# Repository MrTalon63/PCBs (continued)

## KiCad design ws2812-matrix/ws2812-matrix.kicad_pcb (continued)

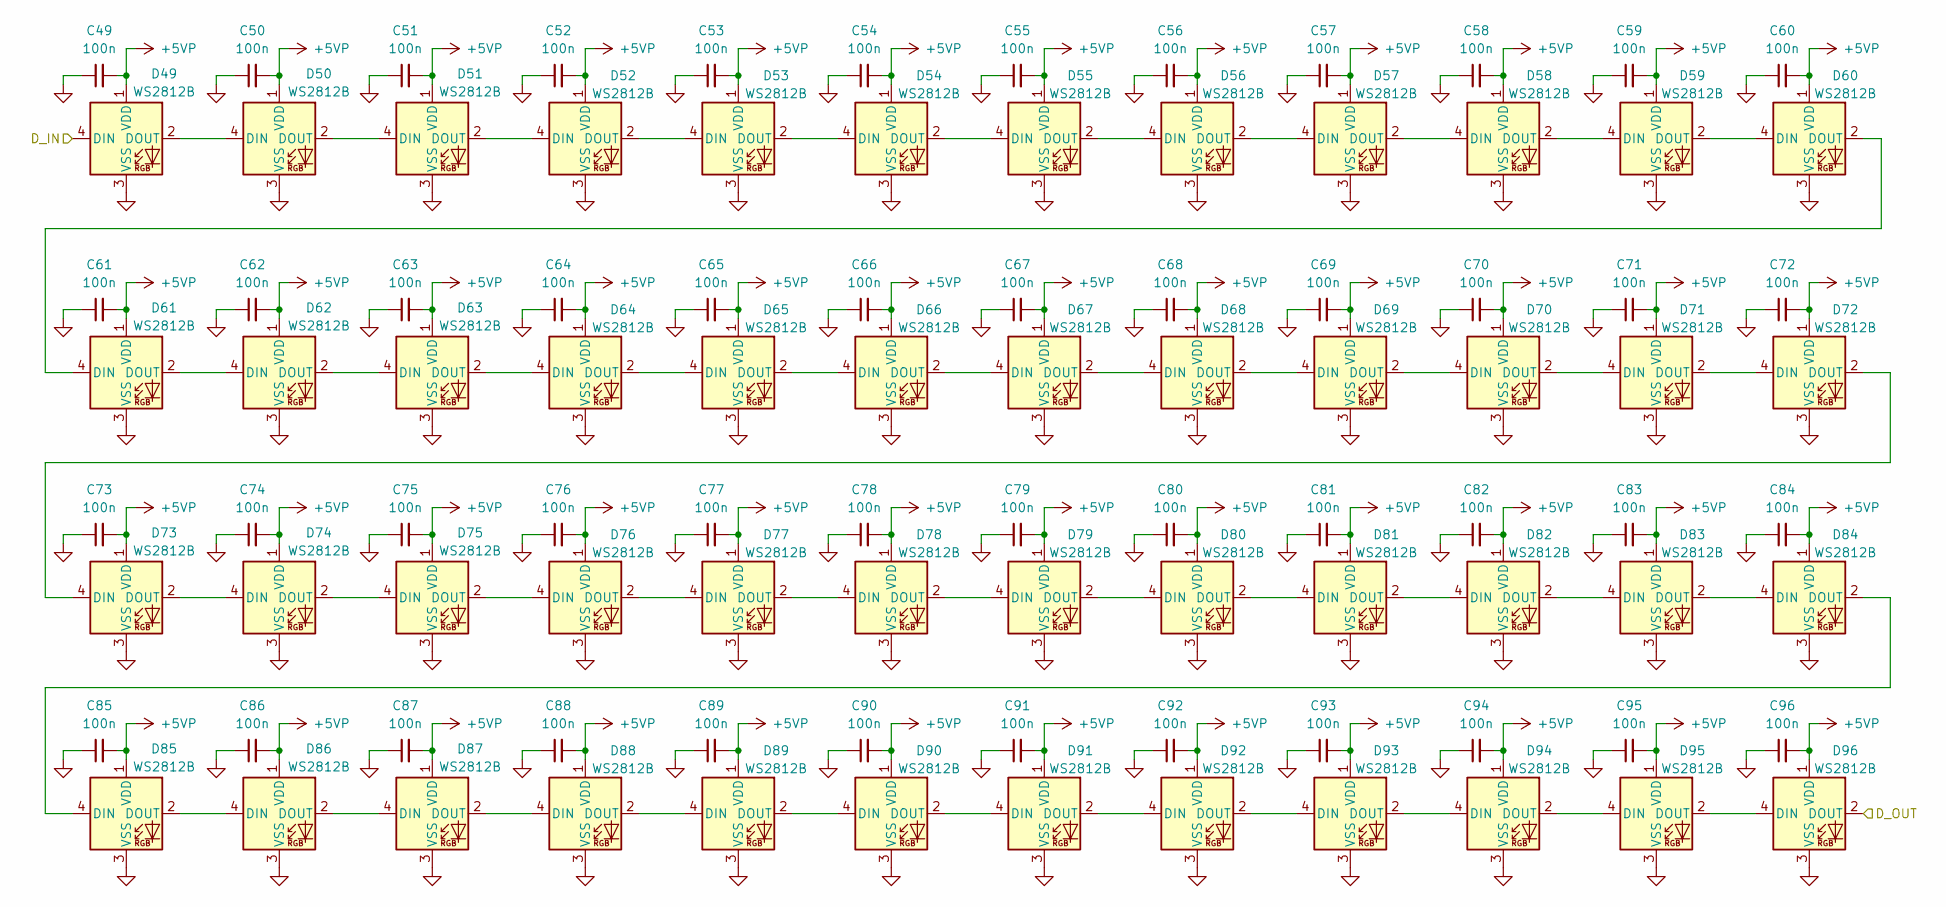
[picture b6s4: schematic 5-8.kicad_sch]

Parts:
C49, C50, C51, C52, C53, C54, C55, C56, C57, C58, C59, C60, C61, C62, C63, C64, C65, C66, C67, C68, C69, C70, C71, C72, C73, C74, C75, C76, C77, C78, C79, C80, C81, C82, C83, C84, C85, C86, C87, C88, C89, C90, C91, C92, C93, C94, C95, C96: 100n; C_0402_1005Metric
D49, D50, D51, D52, D53, D54, D55, D56, D57, D58, D59, D60, D61, D62, D63, D64, D65, D66, D67, D68, D69, D70, D71, D72, D73, D74, D75, D76, D77, D78, D79, D80, D81, D82, D83, D84, D85, D86, D87, D88, D89, D90, D91, D92, D93, D94, D95, D96: WS2812B; LED_WS2812B_PLCC4_5.0x5.0mm_P3.2mm

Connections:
+5VP: C49.2, C50.2, C51.2, C52.2, C53.2, C54.2, C55.2, C56.2, C57.2, C58.2, C59.2, C60.2, C61.2, C62.2, C63.2, C64.2, C65.2, C66.2, C67.2, C68.2, C69.2, C70.2, C71.2, C72.2, C73.2, C74.2, C75.2, C76.2, C77.2, C78.2, C79.2, C80.2, C81.2, C82.2, C83.2, C84.2, C85.2, C86.2, C87.2, C88.2, C89.2, C90.2, C91.2, C92.2, C93.2, C94.2, C95.2, C96.2, D49.1 (VDD), D50.1 (VDD), D51.1 (VDD), D52.1 (VDD), D53.1 (VDD), D54.1 (VDD), D55.1 (VDD), D56.1 (VDD), D57.1 (VDD), D58.1 (VDD), D59.1 (VDD), D60.1 (VDD), D61.1 (VDD), D62.1 (VDD), D63.1 (VDD), D64.1 (VDD), D65.1 (VDD), D66.1 (VDD), D67.1 (VDD), D68.1 (VDD), D69.1 (VDD), D70.1 (VDD), D71.1 (VDD), D72.1 (VDD), D73.1 (VDD), D74.1 (VDD), D75.1 (VDD), D76.1 (VDD), D77.1 (VDD), D78.1 (VDD), D79.1 (VDD), D80.1 (VDD), D81.1 (VDD), D82.1 (VDD), D83.1 (VDD), D84.1 (VDD), D85.1 (VDD), D86.1 (VDD), D87.1 (VDD), D88.1 (VDD), D89.1 (VDD), D90.1 (VDD), D91.1 (VDD), D92.1 (VDD), D93.1 (VDD), D94.1 (VDD), D95.1 (VDD), D96.1 (VDD); also elsewhere on the board
/LEDs/1-4/D_OUT: D49.4 (DIN); also elsewhere on the board
/LEDs/5-8/D_OUT: D96.2 (DOUT); also elsewhere on the board
GND: C49.1, C50.1, C51.1, C52.1, C53.1, C54.1, C55.1, C56.1, C57.1, C58.1, C59.1, C60.1, C61.1, C62.1, C63.1, C64.1, C65.1, C66.1, C67.1, C68.1, C69.1, C70.1, C71.1, C72.1, C73.1, C74.1, C75.1, C76.1, C77.1, C78.1, C79.1, C80.1, C81.1, C82.1, C83.1, C84.1, C85.1, C86.1, C87.1, C88.1, C89.1, C90.1, C91.1, C92.1, C93.1, C94.1, C95.1, C96.1, D49.3 (VSS), D50.3 (VSS), D51.3 (VSS), D52.3 (VSS), D53.3 (VSS), D54.3 (VSS), D55.3 (VSS), D56.3 (VSS), D57.3 (VSS), D58.3 (VSS), D59.3 (VSS), D60.3 (VSS), D61.3 (VSS), D62.3 (VSS), D63.3 (VSS), D64.3 (VSS), D65.3 (VSS), D66.3 (VSS), D67.3 (VSS), D68.3 (VSS), D69.3 (VSS), D70.3 (VSS), D71.3 (VSS), D72.3 (VSS), D73.3 (VSS), D74.3 (VSS), D75.3 (VSS), D76.3 (VSS), D77.3 (VSS), D78.3 (VSS), D79.3 (VSS), D80.3 (VSS), D81.3 (VSS), D82.3 (VSS), D83.3 (VSS), D84.3 (VSS), D85.3 (VSS), D86.3 (VSS), D87.3 (VSS), D88.3 (VSS), D89.3 (VSS), D90.3 (VSS), D91.3 (VSS), D92.3 (VSS), D93.3 (VSS), D94.3 (VSS), D95.3 (VSS), D96.3 (VSS); also elsewhere on the board
unnamed: D49.2 (DOUT), D50.4 (DIN)
unnamed: D50.2 (DOUT), D51.4 (DIN)
unnamed: D51.2 (DOUT), D52.4 (DIN)
unnamed: D52.2 (DOUT), D53.4 (DIN)
unnamed: D53.2 (DOUT), D54.4 (DIN)
unnamed: D54.2 (DOUT), D55.4 (DIN)
unnamed: D55.2 (DOUT), D56.4 (DIN)
unnamed: D56.2 (DOUT), D57.4 (DIN)
unnamed: D57.2 (DOUT), D58.4 (DIN)
unnamed: D58.2 (DOUT), D59.4 (DIN)
unnamed: D59.2 (DOUT), D60.4 (DIN)
unnamed: D60.2 (DOUT), D61.4 (DIN)
unnamed: D61.2 (DOUT), D62.4 (DIN)
unnamed: D62.2 (DOUT), D63.4 (DIN)
unnamed: D63.2 (DOUT), D64.4 (DIN)
unnamed: D64.2 (DOUT), D65.4 (DIN)
unnamed: D65.2 (DOUT), D66.4 (DIN)
unnamed: D66.2 (DOUT), D67.4 (DIN)
unnamed: D67.2 (DOUT), D68.4 (DIN)
unnamed: D68.2 (DOUT), D69.4 (DIN)
unnamed: D69.2 (DOUT), D70.4 (DIN)
unnamed: D70.2 (DOUT), D71.4 (DIN)
unnamed: D71.2 (DOUT), D72.4 (DIN)
unnamed: D72.2 (DOUT), D73.4 (DIN)
unnamed: D73.2 (DOUT), D74.4 (DIN)
unnamed: D74.2 (DOUT), D75.4 (DIN)
unnamed: D75.2 (DOUT), D76.4 (DIN)
unnamed: D76.2 (DOUT), D77.4 (DIN)
unnamed: D77.2 (DOUT), D78.4 (DIN)
unnamed: D78.2 (DOUT), D79.4 (DIN)
unnamed: D79.2 (DOUT), D80.4 (DIN)
unnamed: D80.2 (DOUT), D81.4 (DIN)
unnamed: D81.2 (DOUT), D82.4 (DIN)
unnamed: D82.2 (DOUT), D83.4 (DIN)
unnamed: D83.2 (DOUT), D84.4 (DIN)
unnamed: D84.2 (DOUT), D85.4 (DIN)
unnamed: D85.2 (DOUT), D86.4 (DIN)
unnamed: D86.2 (DOUT), D87.4 (DIN)
unnamed: D87.2 (DOUT), D88.4 (DIN)
unnamed: D88.2 (DOUT), D89.4 (DIN)
unnamed: D89.2 (DOUT), D90.4 (DIN)
unnamed: D90.2 (DOUT), D91.4 (DIN)
unnamed: D91.2 (DOUT), D92.4 (DIN)
unnamed: D92.2 (DOUT), D93.4 (DIN)
unnamed: D93.2 (DOUT), D94.4 (DIN)
unnamed: D94.2 (DOUT), D95.4 (DIN)
unnamed: D95.2 (DOUT), D96.4 (DIN)

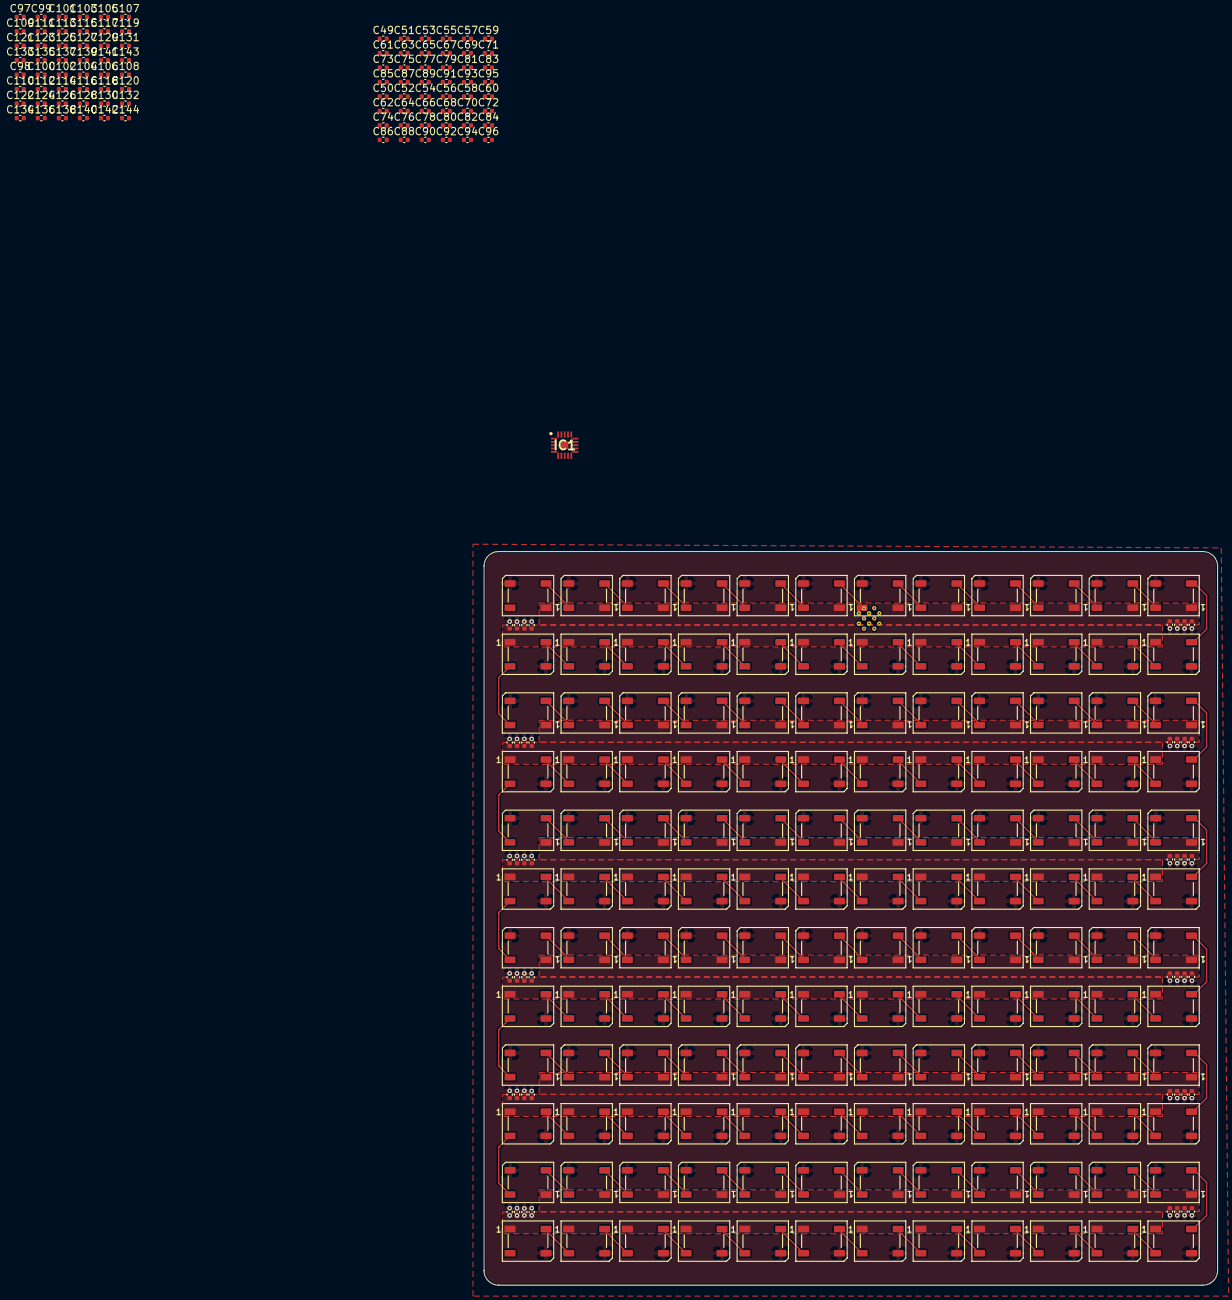
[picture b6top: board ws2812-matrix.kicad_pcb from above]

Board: 4 copper layers, 100.0 x 100.0 mm, 290 parts (1 on the bottom side), 146 nets.
